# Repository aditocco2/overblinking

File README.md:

# Overblinking: The LED Matrix Graduation Cap

_lightslop taken to its logical extreme_

A DIY graduation cap project that shows a slideshow of pictures, GIFs, videos, and scrolling text messages on a 64x64 LED matrix.

Includes a high-performance LED matrix driver, a custom 3D printed mounting system, and a custom PCB.

## Features
- Easy loading of data onto the SD card - no manual downscaling or image dumping needed
- SD card is exposed underneath the cap with a custom PCB, allowing easy replacement of cards
- Mode switch allows you to automatically switch to a less distracting "static mode" during speeches
- Whole system is powered through one battery pack
- Optional rain resistance using an acrylic sheet and 3D printed waterproofing shield
- Automatically initializes/recovers SD cards and survives card swaps
- Only required electronics skill for assembly is through-hole soldering
- Non-destructive design allows you to re-use components for other things post-ceremony (unlike the cap and gown themselves!)

## Build Your Own
For instructions on how to make your own LED matrix graduation cap, read the full guide [here](https://overblinking.substack.com)!

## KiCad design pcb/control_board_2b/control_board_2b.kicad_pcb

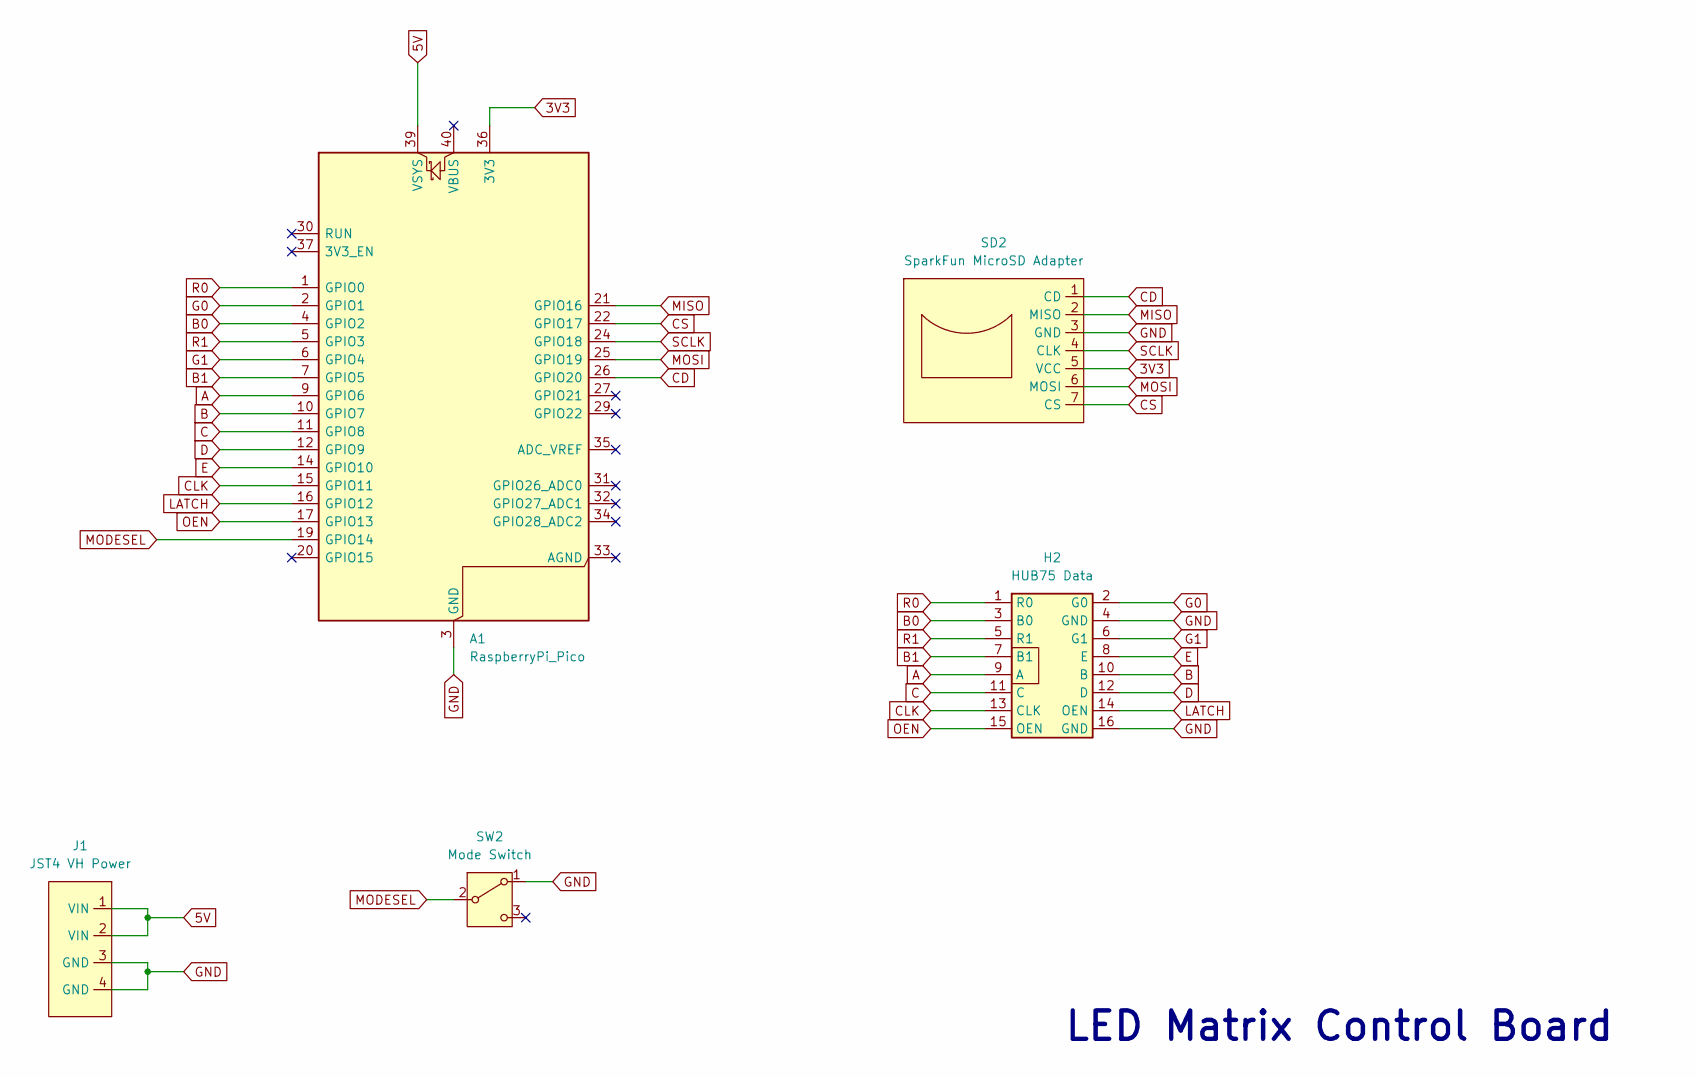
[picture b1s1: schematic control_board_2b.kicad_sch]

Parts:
A1: RaspberryPi_Pico; RaspberryPi_Pico_Common_Unspecified
H2: HUB75 Data; IDC-Header_2x08_P2.54mm_Vertical
J1: JST4 VH Power; JST_VH_B4PS-VH_1x04_P3.96mm_Horizontal
SD2: SparkFun MicroSD Adapter
SW2: Mode Switch; SW_Slide-03_Wuerth-WS-SLTV_10x2.5x6.4_P2.54mm

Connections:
3V3: A1.36 (3V3), SD2.5 (VCC)
5V: A1.39 (VSYS), J1.1 (VIN), J1.2 (VIN)
A: A1.9 (GPIO6), H2.9 (A)
B: A1.10 (GPIO7), H2.10 (B)
B0: A1.4 (GPIO2), H2.3 (B0)
B1: A1.7 (GPIO5), H2.7 (B1)
C: A1.11 (GPIO8), H2.11 (C)
CD: A1.26 (GPIO20), SD2.1 (CD)
CLK: A1.15 (GPIO11), H2.13 (CLK)
CS: A1.22 (GPIO17), SD2.7 (CS)
D: A1.12 (GPIO9), H2.12 (D)
E: A1.14 (GPIO10), H2.8 (E)
G0: A1.2 (GPIO1), H2.2 (G0)
G1: A1.6 (GPIO4), H2.6 (G1)
GND: A1.3 (GND), A1.8 (GND), A1.13 (GND), A1.18 (GND), A1.23 (GND), A1.28 (GND), A1.38 (GND), H2.4 (GND), H2.16 (GND), J1.3 (GND), J1.4 (GND), SD2.3 (GND), SW2.1 (A)
LATCH: A1.16 (GPIO12), H2.14 (OEN)
MISO: A1.21 (GPIO16), SD2.2 (MISO)
MODESEL: A1.19 (GPIO14), SW2.2 (B)
MOSI: A1.25 (GPIO19), SD2.6 (MOSI)
OEN: A1.17 (GPIO13), H2.15 (OEN)
R0: A1.1 (GPIO0), H2.1 (R0)
R1: A1.5 (GPIO3), H2.5 (R1)
SCLK: A1.24 (GPIO18), SD2.4 (CLK)

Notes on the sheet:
LED Matrix Control Board

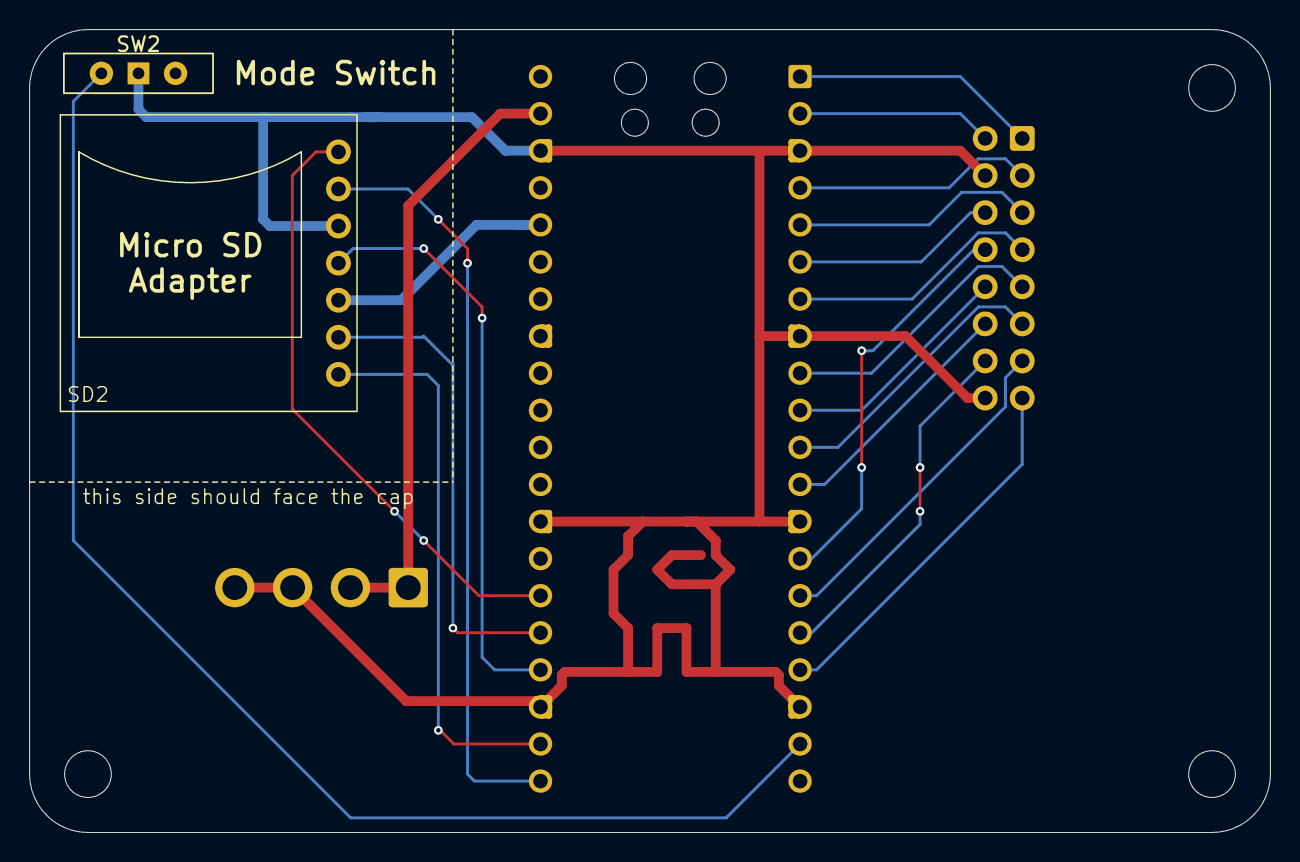
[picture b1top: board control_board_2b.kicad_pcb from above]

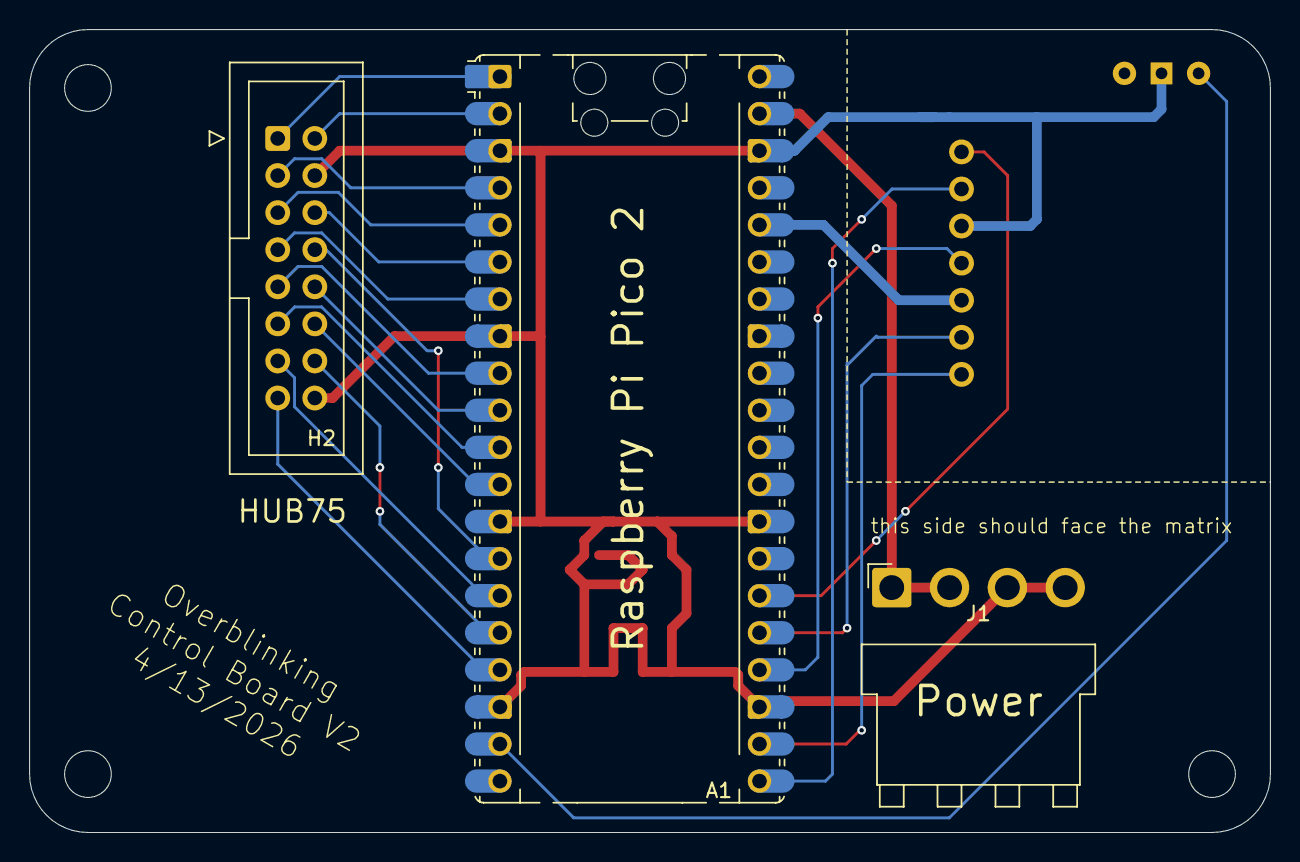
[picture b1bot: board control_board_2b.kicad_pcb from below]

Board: 2 copper layers, 85.0 x 55.0 mm, 5 parts (3 on the bottom side), 23 nets.

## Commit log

2026-02-02 added freertos kernel
    if you see me in embedded say hi
2026-02-04 made it work with FreeRTOS multitasking
2026-02-04 made a basic image to header generation script
2026-02-10 tried some raw sd card shenanigans, inconclusive
2026-02-11 may or may not have passed sd card init
2026-02-11 READING DATA IS WORKING
2026-02-12 improved the sd card driver somewhat
    oaeugh
2026-02-14 multigif support added on python end
2026-02-15 multigif slideshow complete, still need sd card recovery and flicker fix
2026-02-17 SD CARD RECOVERY SORTA KINDA WORKS NOW
2026-02-17 dangerously approaching the DMA rabbit hole
2026-02-23 Working on new CPU-less HUB75 driver
2026-02-24 1000 HZ HUB75 DRIVER IN PROGRESS
    disclaimer: it's 1000 Hz on low brightness. refresh rate depends on the pulse width.
2026-02-27 Non-blocking player with proper SD recovery and a text driver. Ws all around
2026-03-05 bugfixed like everything
2026-03-13 added first few 3d models
2026-03-13 Cleaned up the text driver (?) and made medium fonts
2026-03-15 finished matrix mount v1
2026-03-21 some schematic changes
2026-03-25 static mode works wow
2026-04-11 matrix mount 2 and pcb
2026-04-18 He was forced to pay $40 PCB shipping AGAIN
2026-04-25 made mounting sheet pdf
2026-04-25 improved the media selection algorithm w/ an array shuffle
2026-04-27 improved main code
    recoupled main/player FSMs for less confusion, got improved shuffle working,
    changed mode switch logic to prepare for slide switch instead of button
2026-04-28 fixed a hub75 pio issue that i only noticed when i did scrolling text
    the solution was just to add more delays between clocking in data and doing row stuff/latch stuff
2026-04-30 text = scrolling; code = refactored & clean;
2026-05-03 organized & made first release
